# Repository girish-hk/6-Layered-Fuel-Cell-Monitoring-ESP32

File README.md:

# 6-Layered Fuel Cell Monitoring ESP32

A six-layer fuel cell monitoring PCB designed in KiCad for accurate voltage and current measurement. The system integrates analog signal conditioning, precision ADC interfaces, and an ESP32-S3 microcontroller for data acquisition and processing.

## Features

* 6-layer PCB design
* Fuel cell voltage monitoring
* Fuel cell current monitoring
* ESP32-S3 integration
* Custom KiCad symbols and footprints
* 3D PCB model

## Tools

* KiCad
* ESP32-S3
* Git & GitHub

## Preview

PCB Layout and 3D Render included in the repository.

## Author

Girish H K

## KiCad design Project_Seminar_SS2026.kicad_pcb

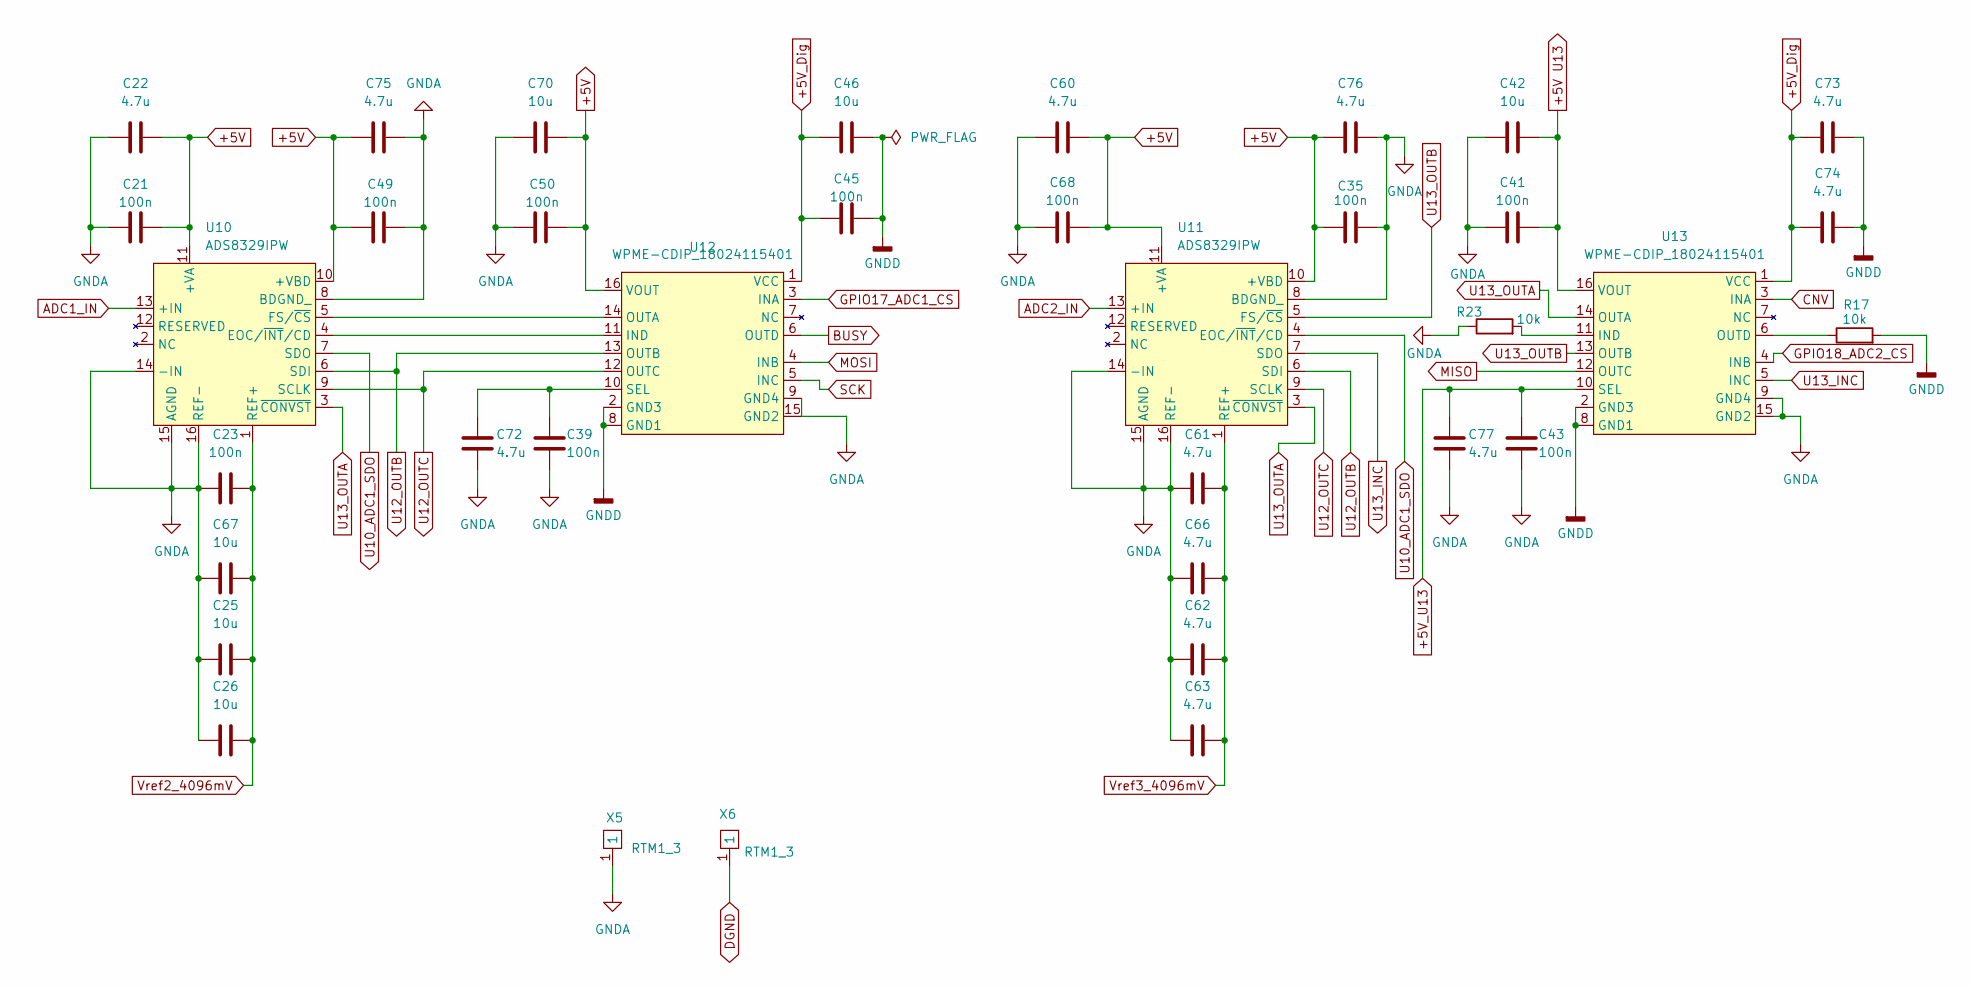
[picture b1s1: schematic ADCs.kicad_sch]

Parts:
C21, C23, C35, C39, C41, C43, C45, C49, C50, C68: 100n; C_0402_1005Metric
C22, C60, C61, C62, C63, C66, C72, C73, C74, C75, C76, C77: 4.7u; C_0402_1005Metric
C25, C26, C42, C46, C67, C70: 10u; C_0402_1005Metric
R17, R23: 10k; R_0402_1005Metric
U10, U11: ADS8329IPW; ADS8329
U12, U13: WPME-CDIP_18024115401
X5, X6: RTM1_3; rtm

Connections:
+5V: C21.2, C22.2, C35.1, C49.1, C50.2, C60.2, C68.2, C70.2, C75.1, C76.1, U10.10 (+VBD), U10.11 (+VA), U11.10 (+VBD), U11.11 (+VA), U12.16 (VOUT); also elsewhere on the board
+5V U13: C41.2, C42.2, U13.16 (VOUT)
+5V_Dig: C45.1, C46.1, C73.1, C74.1, U12.1 (VCC), U13.1 (VCC); also elsewhere on the board
+5V_U13: C43.2, C77.2, U13.10 (SEL)
ADC1_IN: U10.13 (+IN); also elsewhere on the board
ADC2_IN: U11.13 (+IN); also elsewhere on the board
BUSY: U12.6 (OUTD); also elsewhere on the board
CNV: U13.3 (INA); also elsewhere on the board
DGND: X6.1; also elsewhere on the board
GNDA: C21.1, C22.1, C23.1, C25.1, C26.1, C35.2, C39.1, C41.1, C42.1, C43.1, C49.2, C50.1, C60.1, C61.1, C62.1, C63.1, C66.1, C67.1, C68.1, C70.1, C72.1, C75.2, C76.2, C77.1, R23.1, U10.8 (BDGND_), U10.14 (-IN), U10.15 (AGND), U10.16 (REF−), U11.8 (BDGND_), U11.14 (-IN), U11.15 (AGND), U11.16 (REF−), U12.9 (GND4), U12.15 (GND2), U13.9 (GND4), U13.15 (GND2), X5.1; also elsewhere on the board
GNDD: C45.2, C46.2, C73.2, C74.2, R17.2, U12.2 (GND3), U12.8 (GND1), U13.2 (GND3), U13.8 (GND1)
GPIO17_ADC1_CS: U12.3 (INA); also elsewhere on the board
GPIO18_ADC2_CS: U13.4 (INB); also elsewhere on the board
MISO: U13.12 (OUTC); also elsewhere on the board
MOSI: U12.4 (INB); also elsewhere on the board
unnamed: U10.4 (EOC/~INT/CD), U12.11 (IND)
unnamed: U10.5 (FS/~CS), U12.14 (OUTA)
unnamed: C39.2, C72.2, U12.10 (SEL)
unnamed: R23.2, U13.11 (IND)
unnamed: R17.1, U13.6 (OUTD)
SCK: U12.5 (INC); also elsewhere on the board
U10_ADC1_SDO: U10.7 (SDO), U11.4 (EOC/~INT/CD)
U12_OUTB: U10.6 (SDI), U11.6 (SDI), U12.13 (OUTB)
U12_OUTC: U10.9 (SCLK), U11.9 (SCLK), U12.12 (OUTC)
U13_INC: U11.7 (SDO), U13.5 (INC)
U13_OUTA: U10.3 (~CONVST), U11.3 (~CONVST), U13.14 (OUTA)
U13_OUTB: U11.5 (FS/~CS), U13.13 (OUTB)
Vref2_4096mV: C23.2, C25.2, C26.2, C67.2, U10.1 (REF+); also elsewhere on the board
Vref3_4096mV: C61.2, C62.2, C63.2, C66.2, U11.1 (REF+)

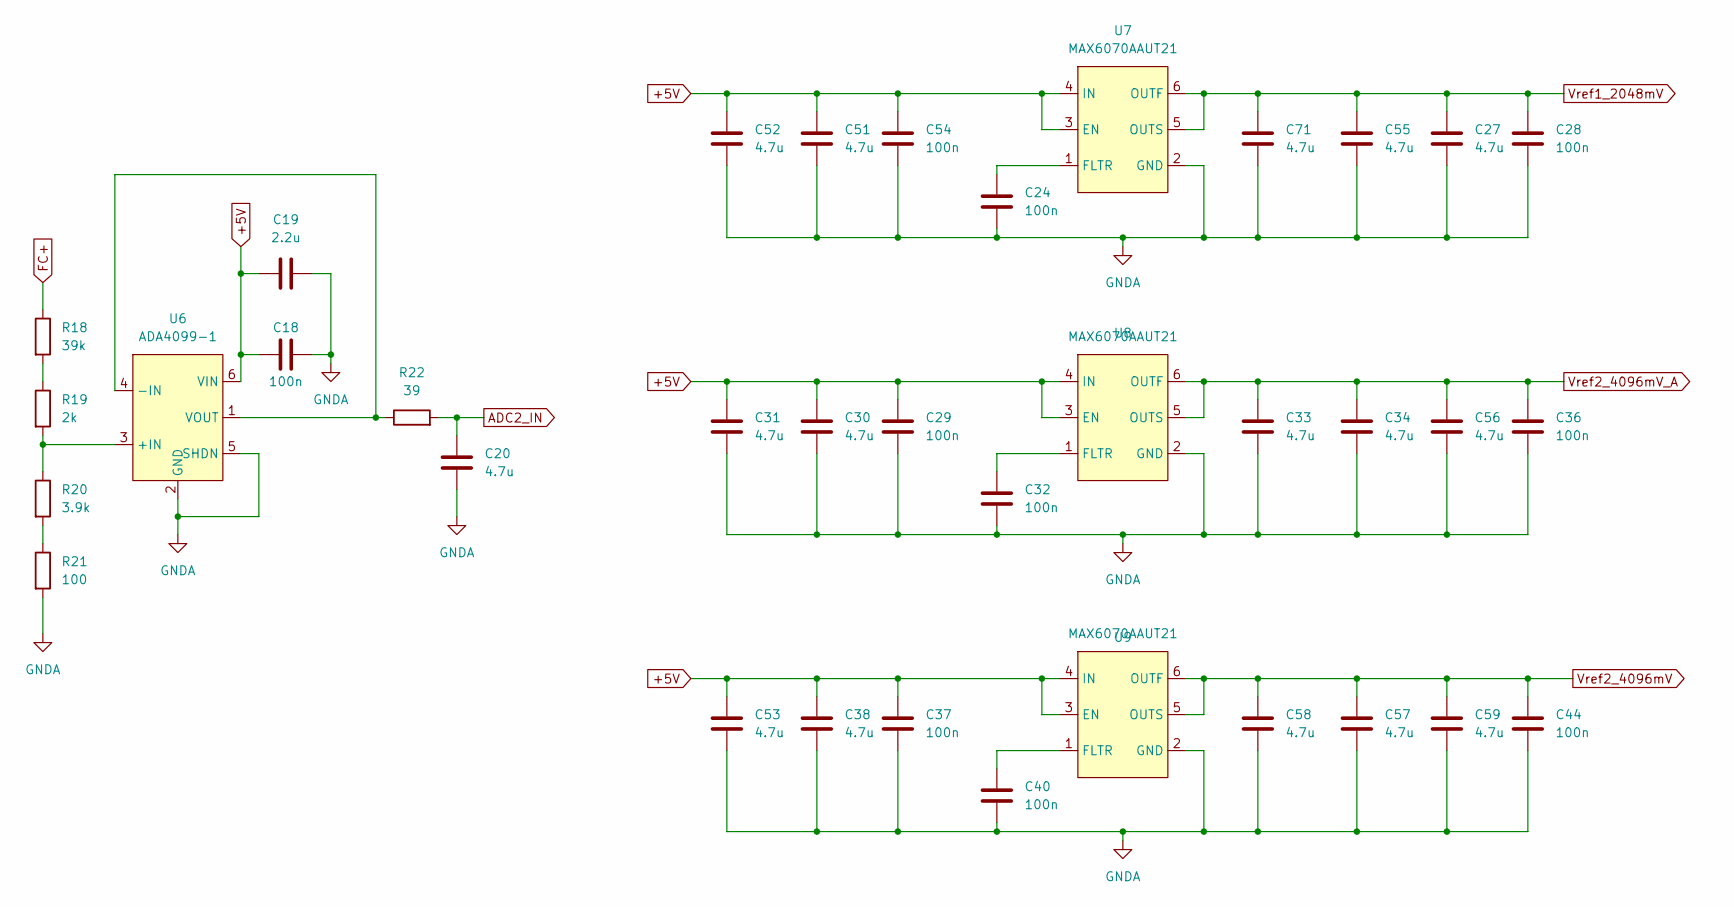
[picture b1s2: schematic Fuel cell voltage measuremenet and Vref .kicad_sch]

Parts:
C18, C24, C28, C29, C32, C36, C37, C40, C44, C54: 100n; C_0402_1005Metric
C19: 2.2u; C_0402_1005Metric
C20, C27, C30, C31, C33, C34, C38, C51, C52, C53, C55, C56, C57, C58, C59, C71: 4.7u; C_0402_1005Metric
R18: 39k; R_0603_1608Metric
R19: 2k; R_0603_1608Metric
R20: 3.9k; R_0603_1608Metric
R21: 100; R_0603_1608Metric
R22: 39; R_0402_1005Metric
U6: ADA4099-1; ADA4099
U7, U8, U9: MAX6070AAUT21; MAX6070

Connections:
+5V: C18.1, C19.1, C29.1, C30.1, C31.1, C37.1, C38.1, C51.1, C52.1, C53.1, C54.1, U6.6 (VIN), U7.3 (EN), U7.4 (IN), U8.3 (EN), U8.4 (IN), U9.3 (EN), U9.4 (IN); also elsewhere on the board
ADC2_IN: C20.1, R22.2; also elsewhere on the board
FC+: R18.1; also elsewhere on the board
GNDA: C18.2, C19.2, C20.2, C24.2, C27.2, C28.2, C29.2, C30.2, C31.2, C32.2, C33.2, C34.2, C36.2, C37.2, C38.2, C40.2, C44.2, C51.2, C52.2, C53.2, C54.2, C55.2, C56.2, C57.2, C58.2, C59.2, C71.2, R21.2, U6.2 (GND), U6.5 (SHDN), U7.2 (GND), U8.2 (GND), U9.2 (GND); also elsewhere on the board
unnamed: R18.2, R19.1
unnamed: R20.2, R21.1
unnamed: R19.2, R20.1, U6.3 (+IN)
unnamed: R22.1, U6.1 (VOUT), U6.4 (-IN)
unnamed: C24.1, U7.1 (FLTR)
unnamed: C32.1, U8.1 (FLTR)
unnamed: C40.1, U9.1 (FLTR)
Vref1_2048mV: C27.1, C28.1, C55.1, C71.1, U7.5 (OUTS), U7.6 (OUTF); also elsewhere on the board
Vref2_4096mV: C44.1, C57.1, C58.1, C59.1, U9.5 (OUTS), U9.6 (OUTF); also elsewhere on the board
Vref2_4096mV_A: C33.1, C34.1, C36.1, C56.1, U8.5 (OUTS), U8.6 (OUTF)

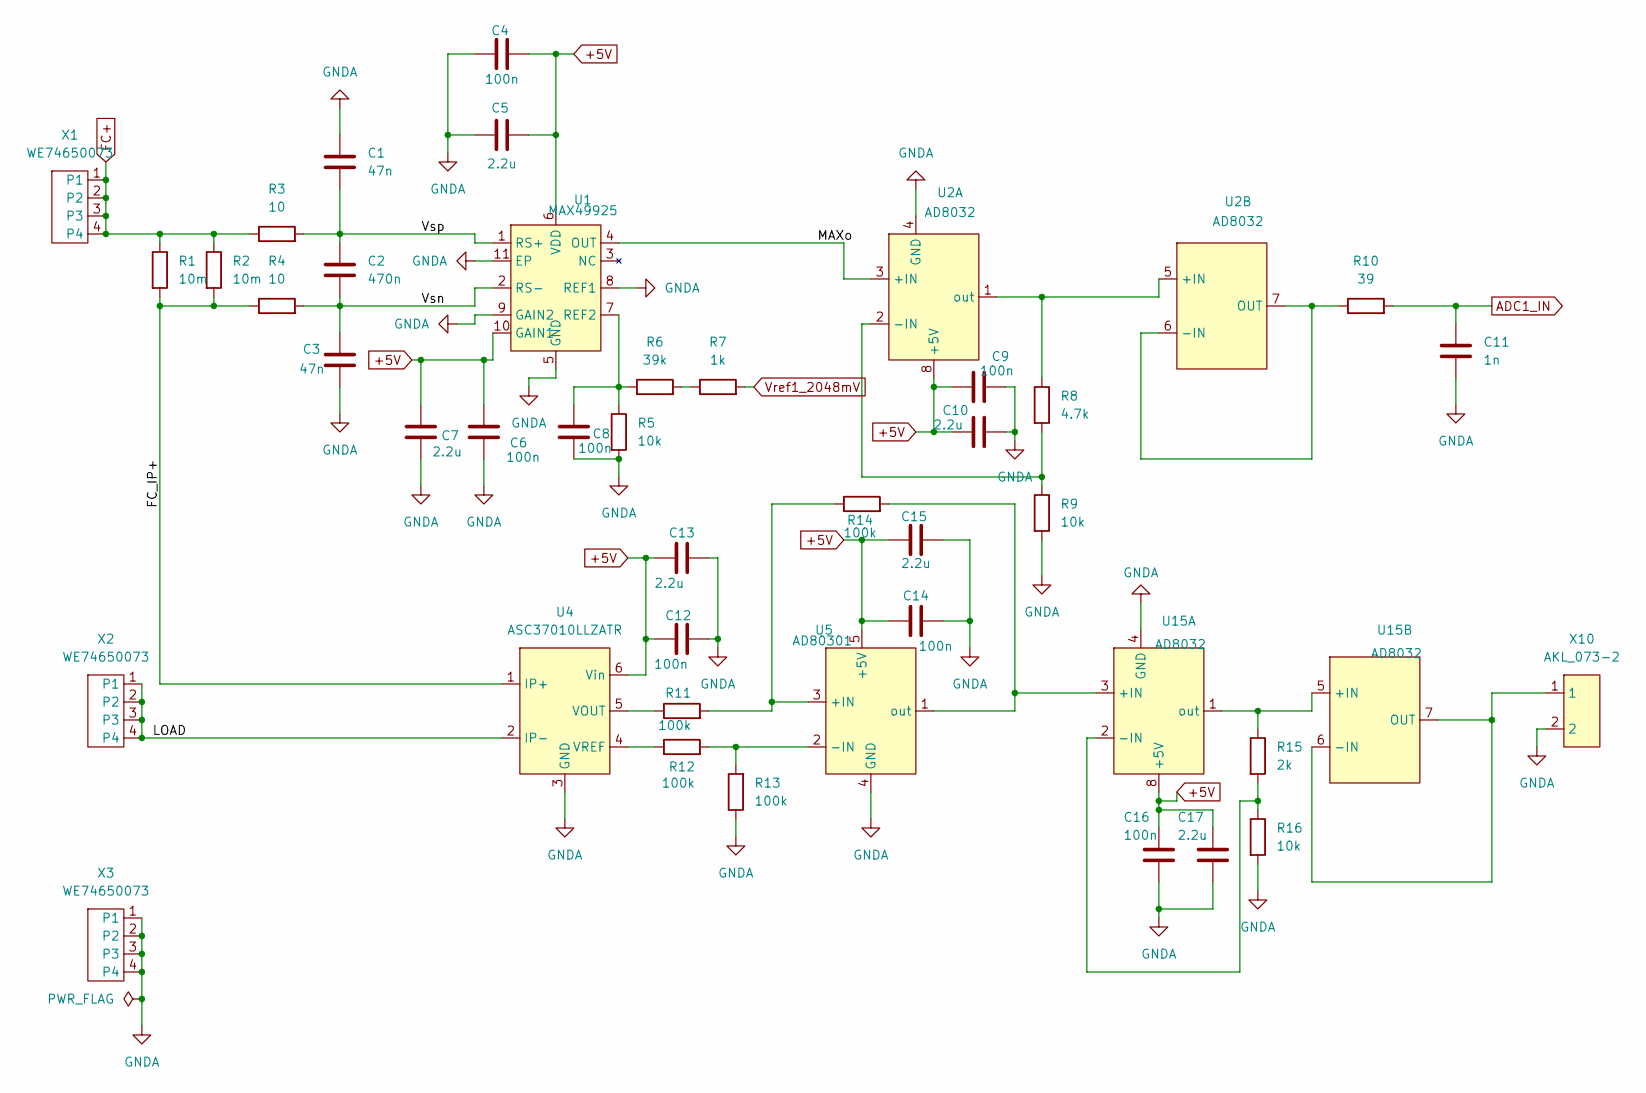
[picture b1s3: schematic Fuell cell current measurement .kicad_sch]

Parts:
C1, C3: 47n; C_0603_1608Metric
C2: 470n; C_0603_1608Metric
C4, C6, C8, C9, C12, C14, C16: 100n; C_0402_1005Metric
C5, C7, C10, C13, C15, C17: 2.2u; C_0402_1005Metric
C11: 1n; C_0402_1005Metric
R1, R2: 10m; R_2512_6332Metric
R3, R4: 10; R_0603_1608Metric
R5, R9, R16: 10k; R_0402_1005Metric
R6: 39k; R_0402_1005Metric
R7: 1k; R_0402_1005Metric
R8: 4.7k; R_0402_1005Metric
R10: 39; R_0402_1005Metric
R11, R12, R13, R14: 100k; R_0402_1005Metric
R15: 2k; R_0402_1005Metric
U1: MAX49925; MAX49925_TDFN10_3x3_EP
U2, U15: AD8032
U4: ASC37010LLZATR; ACS37010LLZATR-030U5
U5: AD80301; AD8031
X1, X2, X3: WE74650073; WP-THRBU REDCUBE 74650073
X10: AKL_073-2; AKLO73-2

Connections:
+5V: C4.2, C5.2, C6.1, C7.1, C9.1, C10.1, C12.1, C13.1, C14.1, C15.1, C16.2, C17.1, U1.6 (VDD), U1.10 (GAIN1), U2.8 (+5V), U4.6 (Vin), U5.5 (+5V), U15.8 (+5V); also elsewhere on the board
/Fuel cell current measurement (page 2)/FC_IP+: R1.2, R2.2, R4.1, U4.1 (IP+)
/Fuel cell current measurement (page 2)/LOAD: U4.2 (IP-), X2.1, X2.2, X2.3, X2.4
/Fuel cell current measurement (page 2)/MAXo: U1.4 (OUT), U2.3 (+IN)
/Fuel cell current measurement (page 2)/Vsn: C2.2, C3.1, R4.2, U1.2 (RS-)
/Fuel cell current measurement (page 2)/Vsp: C1.2, C2.1, R3.2, U1.1 (RS+)
ADC1_IN: C11.1, R10.2; also elsewhere on the board
FC+: R1.1, R2.1, R3.1, X1.1, X1.2, X1.3, X1.4; also elsewhere on the board
GNDA: C1.1, C3.2, C4.1, C5.1, C6.2, C7.2, C8.2, C9.2, C10.2, C11.2, C12.2, C13.2, C14.2, C15.2, C16.1, C17.2, R5.2, R9.2, R13.1, R16.2, U1.5 (GND), U1.8 (REF1), U1.9 (GAIN2), U1.11 (EP), U2.4 (GND), U4.3 (GND), U5.4 (GND), U15.4 (GND), X3.1, X3.2, X3.3, X3.4, X10.2; also elsewhere on the board
unnamed: R6.2, R7.1
unnamed: C8.1, R5.1, R6.1, U1.7 (REF2)
unnamed: R8.2, R9.1, U2.2 (-IN)
unnamed: R8.1, U2.1 (out), U2.5 (+IN)
unnamed: R10.1, U2.6 (-IN), U2.7 (OUT)
unnamed: R11.1, U4.5 (VOUT)
unnamed: R12.1, U4.4 (VREF)
unnamed: R11.2, R14.1, U5.3 (+IN)
unnamed: R12.2, R13.2, U5.2 (-IN)
unnamed: R14.2, U5.1 (out), U15.3 (+IN)
unnamed: R15.2, R16.1, U15.2 (-IN)
unnamed: R15.1, U15.1 (out), U15.5 (+IN)
unnamed: U15.6 (-IN), U15.7 (OUT), X10.1
Vref1_2048mV: R7.2; also elsewhere on the board

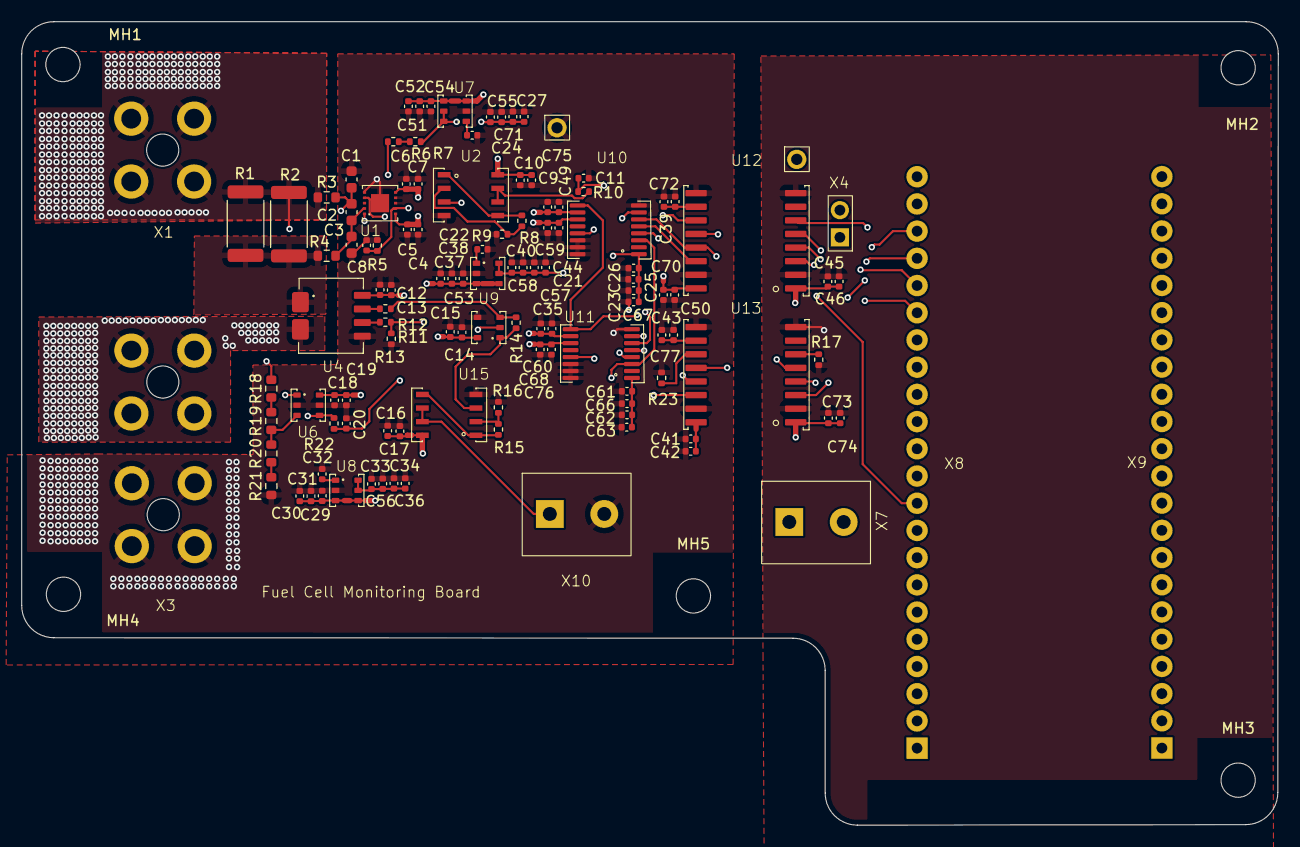
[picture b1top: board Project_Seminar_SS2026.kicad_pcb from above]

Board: 6 copper layers, 117.3 x 75.0 mm, 123 parts (0 on the bottom side), 58 nets.

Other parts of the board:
MH1, MH2, MH3, MH4, MH5: MountingHole_3.2mm_M3
X4: MPE-087; MPE-087-1-002
X7: AKL_073-2; AKLO73-2
X8: BCS-122-L-S-TE_L; BCS-122-L-S-TE
X9: BCS-122-L-S-TE

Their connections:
+5V_Dig: X4.1, X7.1; also elsewhere on the board
BUSY: X8.15; also elsewhere on the board
CNV: X8.20; also elsewhere on the board
DGND: X7.2, X8.22, X9.21, X9.22; also elsewhere on the board
GPIO17_ADC1_CS: X8.10; also elsewhere on the board
GPIO18_ADC2_CS: X8.11; also elsewhere on the board
MISO: X8.19; also elsewhere on the board
MOSI: X8.17; also elsewhere on the board
unnamed: X4.2, X8.21
SCK: X8.18; also elsewhere on the board

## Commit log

2026-06-03 Initial commit of 6-layer fuel cell measurement PCB
2026-06-03 updated 3D models
2026-06-03 Initialize README with project details
    Added project overview, features, tools, and author information.
2026-06-18 Updated PCB design of Solder mask
